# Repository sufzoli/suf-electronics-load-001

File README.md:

# suf-electronics-load-001
Simple micropower electronic load for testing small PSUs

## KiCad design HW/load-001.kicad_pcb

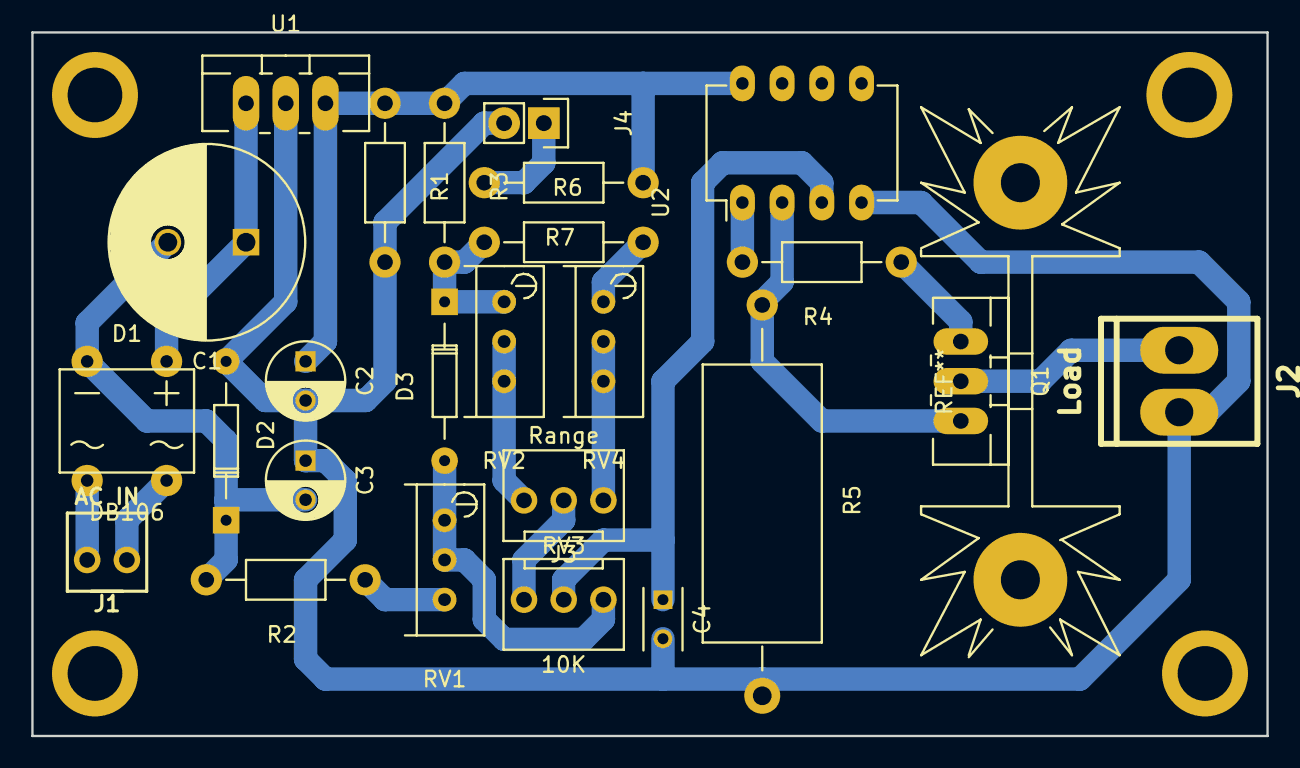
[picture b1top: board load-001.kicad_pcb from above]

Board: 2 copper layers, 79.0 x 45.0 mm, 29 parts (0 on the bottom side), 19 nets.

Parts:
C1: 100uF/35V; C_Radial_D12.5_L25_P5
C2, C3: 100uF/16V; C_Radial_D5_L6_P2.5
C4: 1nF; C_Rect_L4_W2.5_P2.5
D1: DB106; DB-4
D2: 1N4148; Diode_DO-35_SOD27_Horizontal_RM10
D3: BZX55C2V4; Diode_DO-35_SOD27_Horizontal_RM10
J1: AC IN; CONN_NCW254-02S
J2: Load; CONN_NCW396-02S
J3: Range; CONN_NCW254-03S
J4: PWR_LED; Pin_Header_Straight_1x02
MNT_HOLE_3.5, MNT_HOLE_3.5#2, MNT_HOLE_3.5#3, MNT_HOLE_3.5#4: Val**; MNT_HOLE_3.5
Q1: PHP27NQ11T; TO-220_Neutral123_Vertical_LargePads
R1: 5.6K; Resistor_Horizontal_RM10mm
R2: 47; Resistor_Horizontal_RM10mm
R3, R7: 1K; Resistor_Horizontal_RM10mm
R4: 100; Resistor_Horizontal_RM10mm
R5: 1; Resistor_Horizontal_RM25mm
R6: 100K; Resistor_Horizontal_RM10mm
RV1: 50; Potentiometer_Bourns_3296W_3-8Zoll_Inline_ScrewUp
RV2: 10K; Potentiometer_Bourns_3296W_3-8Zoll_Inline_ScrewUp
RV3: 10K; CONN_NCW254-03S
RV4: 50K; Potentiometer_Bourns_3296W_3-8Zoll_Inline_ScrewUp
U1: LM7812; TO-220_Neutral123_Vertical_LargePads
U2: TS358; DIP-8_W7.62mm_LongPads

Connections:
GND: C2.2, C3.1, C4.2, D2.2, J2.2, J4.2, R1.2, R5.2, U1.2, U2.4
unnamed: C1.1, D1.4, U1.1
unnamed: C1.2, C3.2, D1.1, D2.1, R2.2
unnamed: C4.1, RV3.2, U2.3
unnamed: D1.2, J1.2
unnamed: D1.3, J1.1
unnamed: D3.1, R3.2, R6.1, RV2.1
unnamed: D3.2, RV1.1, RV1.2, RV3.3
unnamed: J2.1, Q1.2
unnamed: J3.1, RV4.2, RV4.3
unnamed: J3.2, RV3.1
unnamed: J3.3, RV2.2, RV2.3
unnamed: J4.1, R7.2
unnamed: Q1.1, R4.1
unnamed: Q1.3, R5.1, U2.2
unnamed: R2.1, RV1.3
unnamed: R4.2, U2.1
unnamed: R6.2, RV4.1
VCC: C2.1, R1.1, R3.1, R7.1, U1.3, U2.8

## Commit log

2016-01-21 Schematic diagram - unfinished
2016-01-26 Finished hardware design and 3D design
2021-03-20 Add 3D design
